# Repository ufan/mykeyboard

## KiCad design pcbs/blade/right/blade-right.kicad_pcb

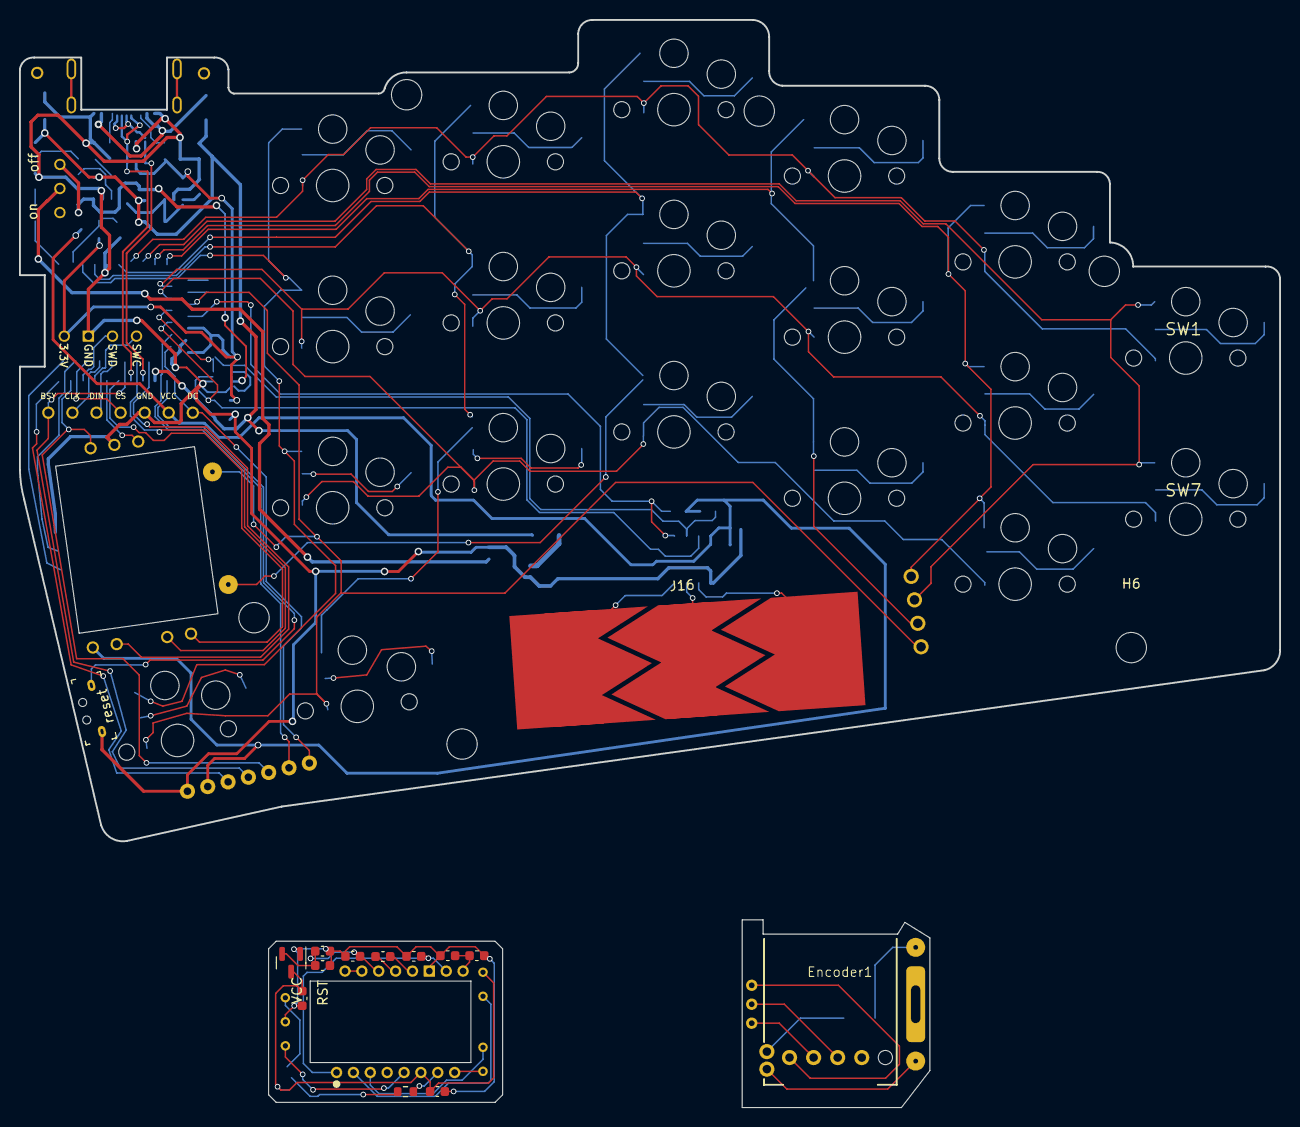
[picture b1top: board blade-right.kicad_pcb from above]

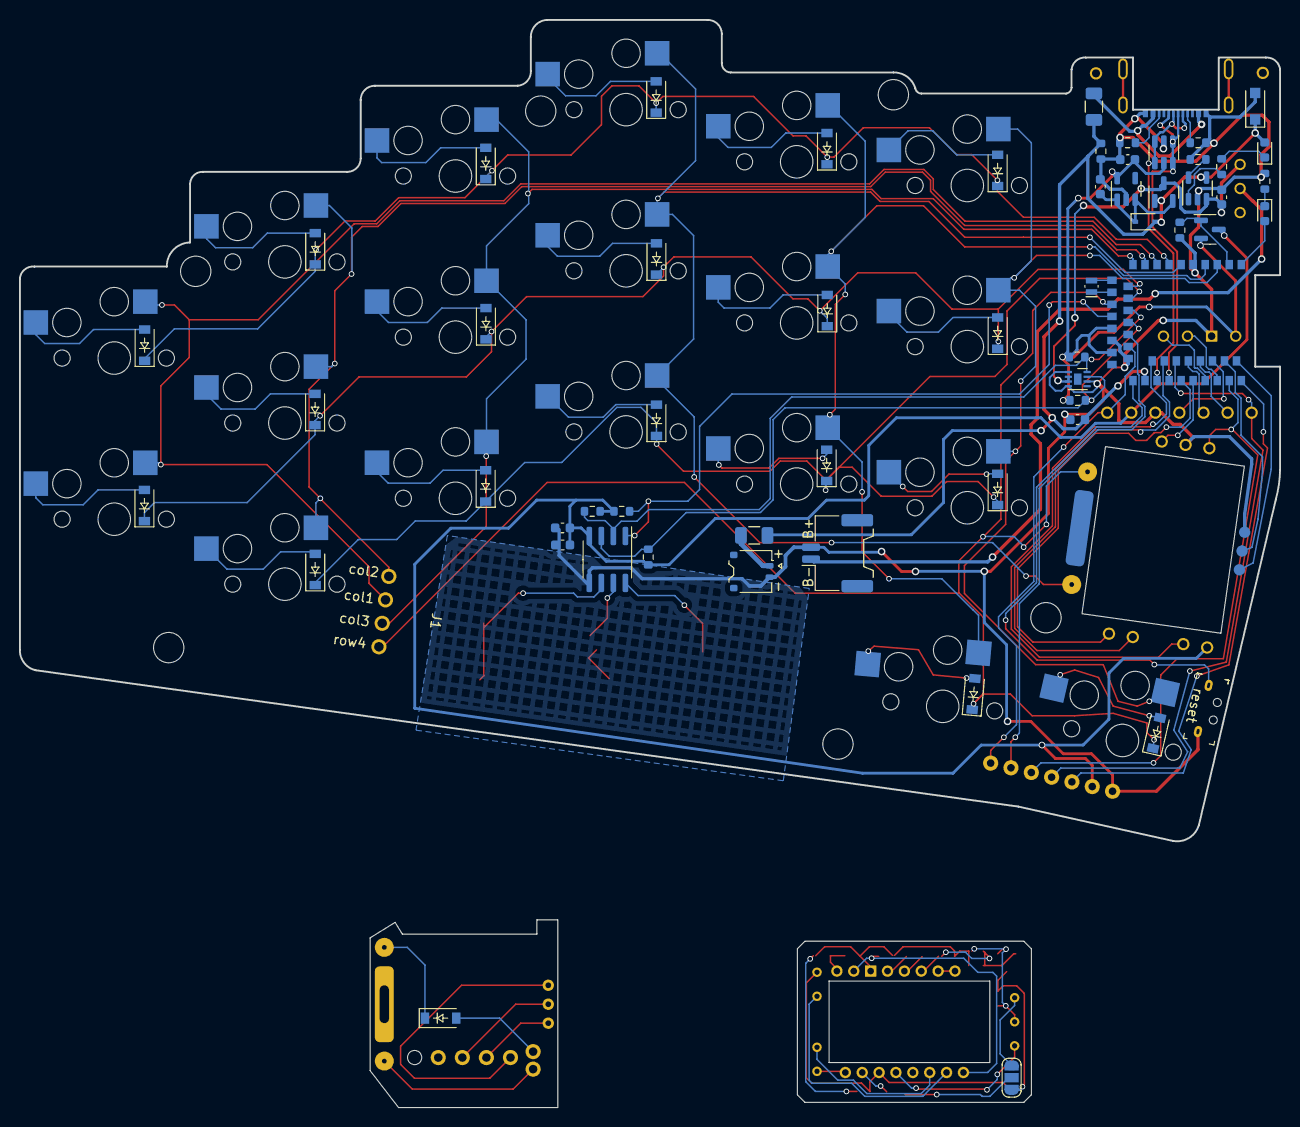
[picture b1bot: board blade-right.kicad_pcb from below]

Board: 2 copper layers, 133.0 x 86.7 mm, 106 parts (61 on the bottom side), 94 nets.

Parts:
Bat_main1: Conn_Battery_solderable; Molex_Panelmate_53780-0270_1x02-1MP_P1.25mm_Horizontal
C1, C3: 4.7u; C_0603_1608Metric
C2: 10u; C_0603_1608Metric
C4: 0.1u; C_0603_1608Metric
C5: 10n; C_0603_1608Metric
C6, C11: 100n; C_0603_1608Metric
C7: 3.3u/16V; C_0603_1608Metric
C8: 100n (X7R); C_0603_1608Metric
C9, C10: 1u; C_0603_1608Metric
C12: 10u (X7R); C_0603_1608Metric
C13: 10n (X7R); C_0603_1608Metric
C14: 0.1uF; C_0603_1608Metric
C15: 1uF; C_0603_1608Metric
D1, D2, D3, D4, D5, D6, D7, D8, D9, D10, D11, D12, D14, D15, D16, D17, D18, D19, D20, D21: 1N4148W; Diode
D22: BAT60B; D_SOD-323
D23: BLUE; LED_0603_1608Metric
D24: RED; LED_0603_1608Metric
D25: SMF9.0CA; D_SOD-123F
Encoder1: RotaryEncoder; Panasonic_EVQWGD001_Latest
F1, F2: 500mA; Fuse_1206_3216Metric
H1, H2, H3, H4, H5, H6: MountingHole; MountingHole_3.2mm_M3_DIN965
J1: expantion1; Magnetic-PogoPin-1x04-Female
J3: Conn_01x07; PMW3610-Ref-Male
J5: Conn_01x05; Panasonic_EVQWGD001_Ref_Male
J9: Conn_Display_general; Conn_Display_MountHole
J10: Conn_01x07; Magnetic-PogoPin-1x07-Male
J11: Conn_01x04_Female; PinHeader_1x04_P2.54mm_Vertical
J12: USB-C USB 2.0 MC-372; nrfmicro_USB-C_C168688
J16: Conn_01x03_Male; TouchSlider-3_36x12mm
JP1: SolderJumper_3_Open; SolderJumper-3_P1.3mm_Open_RoundedPad1.0x1.5mm_NumberLabels
Q1, Q2: AO3407; SOT-23
R1, R2: 5.1K; R_0603_1608Metric
R3: 100K; R_0603_1608Metric
R4, R6: 1K; R_0603_1608Metric
R5, R13: 2M; R_0603_1608Metric
R7: 5K; R_0603_1608Metric
R8, R9: 5.1k; R_0603_1608Metric
R10, R11, R12: 10k; R_0603_1608Metric
Ref1: Conn_01x05; Panasonic_EVQWGD001_Ref
Ref2: Conn_1x07; PMW3610-Ref
SW1, SW2, SW3, SW4, SW5, SW6, SW7, SW8, SW9, SW10, SW11, SW12, SW14, SW15, SW16, SW17, SW18, SW19, SW20: SW_PUSH-kbd; Kailh_Choc_Hotplug
SW_Bat1: SW_Battery-kbd; SW_BSI10
SW_Reset1: SW_RESET-kbd; SW_Reset_vertical
U1: E73-2G4M08S1C; E73-2G4M08S1C-52840
U2: SRV05-4
U3: XC6220B331MR-G; SOT-23-5
U4: MAX17048; MAX17048-TDFN-8-1EP_2x2mm_P0.5mm_EP0.8x1.2mm
U5: TP4054; SOT-23-5
U6: PMW3610
U7: MCP1700-1802E-TT; SOT-23
U8: CAP1203; SOIC-8_3.9x4.9mm_P1.27mm
WirelessCharger1: Conn_01x02_Female; JST_ACH_BM02B-ACHSS-GAN-ETF_1x02-1MP_P1.20mm_Vertical
X1: 32.768 kHz; Crystal_SMD_MicroCrystal_CM9V-T1A-2Pin_1.6x1.0mm

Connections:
/COL4: Ref1.5, SW4.1, SW10.1, SW16.1, U1.6 (P1.13)
/MUX1: J9.dc, J10.7, U1.22 (P0.07)
/MUX2: J9.bsy, J10.4, U1.32 (P0.20)
/MUX3: J10.5, Ref2.rst, U1.41 (P0.09/NFC1)
/ROW4: D19.1 (K), D20.1 (K), J1.4, Ref1.4, U1.15 (P0.05/AIN3)
/VCC: C14.1, C15.1, J9.vcc, J10.2, Q2.3 (D), R10.1, R11.1, R12.1, Ref2.vcc, U8.4 (VDD)
/encoder/COL_4: Encoder1.S1, J5.col
/encoder/ENC_A: Encoder1.A, J5.a
/encoder/ENC_B: Encoder1.B, J5.b
/encoder/GND: Encoder1.com (COM), J5.gnd
/encoder/ROW_4: D21.1 (K), J5.row
/keyboard/COL_1: J1.2, SW1.1, SW7.1, U1.8 (P0.29/AIN5)
/keyboard/COL_2: J1.1, SW2.1, SW8.1, SW14.1, U1.9 (P0.31/AIN7)
/keyboard/COL_3: J1.3, SW3.1, SW9.1, SW15.1, U1.10 (P0.30/AIN6)
/keyboard/COL_5: SW5.1, SW11.1, SW17.1, SW19.1, U1.4 (P0.28/AIN4)
/keyboard/COL_6: SW6.1, SW12.1, SW18.1, SW20.1, U1.3 (P0.03/AIN1)
/keyboard/ROW_1: D1.1 (K), D2.1 (K), D3.1 (K), D4.1 (K), D5.1 (K), D6.1 (K), U1.7 (P0.02/AIN0)
/keyboard/ROW_2: D7.1 (K), D8.1 (K), D9.1 (K), D10.1 (K), D11.1 (K), D12.1 (K), U1.12 (P0.26)
/keyboard/ROW_3: D14.1 (K), D15.1 (K), D16.1 (K), D17.1 (K), D18.1 (K), U1.14 (P0.06)
/mcu/0.10/nfc: J10.3, U1.43 (P0.10/NFC2)
/mcu/0.12/hi: J10.6, U1.20 (P0.12)
/mcu/0.13: Ref2.intr (motion), U1.33 (P0.13)
/mcu/0.15/hi: Ref2.sdio, U1.28 (P0.15)
/mcu/0.17/hi: Ref2.sclk, U1.30 (P0.17)
/mcu/0.22/hi: J9.din, U1.34 (P0.22)
/mcu/0.24: Ref2.ncs, U1.35 (P0.24)
/mcu/1.00/hi: J9.clk, U1.36 (P1.00)
/mcu/1.02: J9.cs, U1.38 (P1.02)
/mcu/1.04: Ref1.2, U1.40 (P1.04)
/mcu/1.06: Ref1.3, U1.42 (P1.06)
/mcu/BLUE_LED: D23.2 (A), U1.1 (P1.11)
/mcu/D+: J12.A6 (D+), J12.B6 (D+), U1.31 (USB_D+), U2.1 (IO1), U2.6 (IO4)
/mcu/D-: J12.A7 (D-), J12.B7 (D-), U1.29 (USB_D-), U2.3 (IO2), U2.4 (IO3)
/mcu/RESET: SW_Reset1.1, U1.26 (P0.18/RESET)
/mcu/SCL: R9.2, R10.2, U1.18 (P0.04/AIN2), U4.7 (SCL), U8.3 (SMCLK)
/mcu/SDA: R8.2, R11.2, U1.16 (P0.08), U4.8 (SDA), U8.2 (SMDATA)
/mcu/SWC: J11.2, U1.39 (SWDCLK)
/mcu/SWD: J11.1, U1.37 (SWDIO)
/mcu/VBAT: C4.1, Q1.3 (D), SW_Bat1.3 (C), U4.2 (CELL), U4.3 (VDD), U5.3 (VBAT)
/mcu/VBUS: C1.1, D22.2 (A), D24.2 (A), D25.1 (A1), F1.1, F2.1, Q1.1 (G), R3.1, U1.27 (VBUS), U5.4 (VDD)
/mcu/VCC_CTRL: Q2.1 (G), R5.1, U1.2 (P1.10)
/mcu/VRAW: Bat_main1.bat+ (Bat+), SW_Bat1.2 (B)
/mcu/nRF_VDD: C3.1, J11.4, Q2.2 (S), R8.1, R9.1, U1.19 (VDD), U1.23 (VDDH), U2.5 (VP), U3.5 (VOUT)
/touchbar/INT: R12.2, U1.17 (P1.09), U8.1 (ALERT#)
/trackball/1.8V: C6.1, C7.1, C10.1, U6.14 (VDD), U7.2 (VO)
/trackball/3.3V: C9.2, C11.1, J3.vcc, JP1.3 (B), U6.6 (VDDIO), U7.3 (VI)
/trackball/GND: C5.2, C6.2, C7.2, C9.1, C10.2, C11.2, C12.2, C13.2, J3.gnd, U6.11 (GND), U7.1 (GND)
/trackball/MOTION: J3.intr (motion), U6.8 (MOTION)
/trackball/NCS: J3.ncs, U6.5 (NCS)
/trackball/NRESET: J3.rst, JP1.1 (A)
/trackball/SCLK: J3.sclk, U6.3 (SCLK)
/trackball/SDIO: J3.sdio, U6.2 (SDIO)
GND: Bat_main1.bat- (Bat-), C1.2, C2.2, C3.2, C4.2, C14.2, C15.2, D25.2 (A2), J9.gnd, J10.1, J11.3, J12.A1 (GND), R1.2, R2.1, R3.2, R4.2, R5.2, R7.2, Ref1.1, Ref2.gnd, SW_Reset1.2, U1.5 (GND), U1.21 (GND), U1.24 (GND), U2.2 (VN), U3.2 (GND), U4.1 (CTG), U4.4 (GND), U4.6 (QSTRT), U5.2 (VSS), U8.5 (GND), WirelessCharger1.gnd
unnamed: C2.1, D22.1 (K), Q1.2 (S), U3.1 (VIN), U3.3 (EN)
unnamed: C5.1, U6.1 (+VCSEL), U6.10 (PASS_T)
unnamed: C8.1, U6.13 (CN)
unnamed: C8.2, U6.12 (CP)
unnamed: C12.1, C13.1, U6.9 (VCP)
unnamed: D1.2 (A), SW1.2
unnamed: D2.2 (A), SW2.2
unnamed: D3.2 (A), SW3.2
unnamed: D4.2 (A), SW4.2
unnamed: D5.2 (A), SW5.2
unnamed: D6.2 (A), SW6.2
unnamed: D7.2 (A), SW7.2
unnamed: D8.2 (A), SW8.2
unnamed: D9.2 (A), SW9.2
unnamed: D10.2 (A), SW10.2
unnamed: D11.2 (A), SW11.2
unnamed: D12.2 (A), SW12.2
unnamed: D14.2 (A), SW14.2
unnamed: D15.2 (A), SW15.2
unnamed: D16.2 (A), SW16.2
unnamed: D17.2 (A), SW17.2
unnamed: D18.2 (A), SW18.2
unnamed: D19.2 (A), SW19.2
unnamed: D20.2 (A), SW20.2
unnamed: D21.2 (A), Encoder1.S2
unnamed: D23.1 (K), R4.1
unnamed: D24.1 (K), R6.1
unnamed: F1.2, J12.A4 (VBUS)
unnamed: F2.2, WirelessCharger1.vbus
unnamed: J12.A5 (CC1), R1.1
unnamed: J12.B5 (CC2), R2.2
unnamed: J16.1, U8.8 (CS1)
unnamed: J16.2, U8.7 (CS2)
unnamed: J16.3, U8.6 (CS3)
unnamed: JP1.2 (C), R13.1
unnamed: R6.2, U5.1 (STAT)
unnamed: R7.1, U5.5 (PROG)
unnamed: R13.2, U6.7 (NRESET)
unnamed: U1.11 (P0.00/XL1), X1.2
unnamed: U1.13 (P0.01/XL2), X1.1
unnamed: U6.15 (XYLASER), U6.16 (-VCSEL)
